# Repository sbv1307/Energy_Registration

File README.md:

# **Energy registration**
###### **Version 2.0.0**

This Arduino project will monitor the open collector output on a number of Carlo Gavazzi energy meters Type EM23 DIN and/or Type EM111.
The pulses will be counted and turned into number of kilo watt hours (kWh).

Upon request, the pulses counted (presented in kWh) will be pushed to a Google Sheet through a local webhook (A web site which basically "translate" HPPT to HTTPS).

Each meter monitored, will be connected to a digital imput, as well as the interrupt pin (See Emergy Registration Schematics.pdf for details).

Upon a HTTP GET pushToGoogle request (http://<Arduino IP address>/pushToGoogle), the sketch will return a HTML webpage, showing the current meter valeus, 
and initiate a HTTP GET request towards a local webHook, with the meter values, as the GET query values.

A HTTP GET meterValue request (http://<Arduino IP address>/meterValue) will return a webpage showing the current meter valeus.
 
A HTTP GET meterValue?meter<n>=<nn>, will set the counter to the provided value for the specified energy meter.
The value <n> represent the energy meter 1-7 and nn the actual energy meter value as readden on the meter, with two dicmals but entered without the decimal seperator!
(http://<Arduino IP address>/meterValue?meter1=1234567 will set the value for energy meter number one to 12345.67)

Notes:
The sketch monitors interrupt pin 2 for a FALLING puls and then reads the defined channelPins and register pulses for each pin.
The interruptfunction has a catch: It enters a "while pin 2 is low" loop, and stays there, until the interrupt is released.
This is against all recomendations, saying Interruptfunctions should be very short. 

However, in order to handle the problem with overlapping pulses from more meters, the interruptfunction will read the channels over and over,
without re-reading channels that allready has been read active (low). This way all pulses on all channels will be read.

Example: Tree meters generate tree pulses as shown below:
```bash
          _______        _______
Meter #1:        |______|
             _______        _______
Meter #2:           |______|
                _______        _______
Meter #3:              |______|

```
A pulse from meter #1 will activate the Interrupt Service Rutine (ISR), which startes the "while pin 2 is low" loop. When the pulse on meter #2 appears, while the pulse on meter #1 is still active, the ISR will stay active, when the puls on meter #1 dissapears. Then same happens when the pulse from meter #3 appears.
The "while pin 2 is low" loop read all non-read input pins, meaning: when a pin has been read as active (LOW), then pin will be read as readden, and wil not be re-read.

When the puls (the puls in meter #3) is released, the ISR ends. Then main loop will update the counter for each readden input pin, at reset the the status for the input pin.

 Version history:
  * 2.0.0 - Arduino SW project now merged with KiCad Hardware, and this version surpports the new HW design
 *         1 - LED_BUILTIN on Pin #9 has stopped woring. Pin A3 will be used instead. LED_PIN changed to LED_PIN - 
 *             HOWEVER!!! It has turned out, that it was set incrrrectly by the entrepreter. Hovering over the LED_BULTIN variable indicate it expands to 13 and not 9.
 *             Setting LED_PIN to 9, makes the LED light.
 *             Since the Hardware prototype, was made to use PIN 17, Pin 17 will be used for LED_PIN in this version.
 *         2 - Channels extenced to 8 instead of 7. Noe includeing Pin A2 
 * 0.2.3 - BUILTIN_LED has stopped working - NEED INVESTIGATION AND CODE IMPLEMTATION
 * 0.2.2 - Post powerup data to google sheets (data, and the comment (Power Up))
 * 0.2.1 - Cleaning up entries used for verifying pulscounts - No functional changes.
 * 0.2.0 - Meters, which only gives 100 pulses pr. kWh, were registered as if they gave a thousenth. Might be an issue by adding "1.000 / (double)PPKW[ii]" (0.01) to the previous counts.
 *         Since 1.000 / "(double)PPKW[ii]" might now be exactly 0.01 but maybe 0.009nnnnnnnnn, which could sum up the deffrence.
 *         SO - This version 0.2.0 will count pulses (integers). 
 *         Notes to be taken here - Mixing the types long and int, can give strange results (sometimes).
 *          - Implement: Remove SD update after each pulsecount, marked: "// V0.1.4_change (1)" in ver. 0.1.4
 *          - Implement: Flashing LED_BUILTI handled by calls to millis(), marked : "// V0.1.4_change (3)" in ver. 0.1.4.
 *          - SD Updates are done for every 10 pulses or every 30 minutes (only if pulses have been registred).
 * 0.1.4 - In an attempt to investigate lost registrations, writing every update to SD will be changed (changes marked // V0.1.4_change):
 *         1 - Remove SD update after each pulsecount marked: // V0.1.4_change (1)
 *         2 - SD is updated after each call to HTTP GET meterValue request (http://<Arduino IP address>/meterValue) marked: // V0.1.4_change (2)
 *         3 - Flashing the LED_BUILTI has handeled by the time it took to write to SD. Flashing LED_BUILTI will be handled by calls to millis() marked : // V0.1.4_change (3)
 * 
 * 0.1.3 - Due to capacity limitations in version 0.1.2, this version build upon version 0.1.1
 *       - This version is to trace why pulse registrations are lost.
 *       - Screesed in the HTML <form> element form Version 0.2.1 - Makes energymeter settings much easier
 *       - Dividing entered metervalues by 100, to avodi having to enter dicimal point (a dot) when enter metervalues
 *       - Corrected BUGs in getQuery(EthernetClient localWebClient)
 *       - Error dinvestigations marked: TO_BE_REMOVED
 *       - Added further #ifdef sections.
 *       - Inserted a function call to setMeterDataDefaults in function getQuery. If Metervalue for Meter 1 is nigative, metervalues are reset
 * 0.1.2 - N O T E !!!! - Changes exceeded limit for: Low memory available, stability problems may occur.
 *         Change in HTML presentation of energy meter values. Describing text. e.g. "Værksted" added to the informaiotn: "Meter <n>".
 *       - Introduces IP configuration for Arduino Ethernet shield attached to Arduino UNO. Define ARDUINO_UNO_DEBUG
 * 0.1.1 - Web server and web client funktionality added.
 * 0.1.0 - Initial commit - This versino is a merger of two lab tests: "EnergyRegistration" and "LocalWebHook-with-server-for-Arduino".

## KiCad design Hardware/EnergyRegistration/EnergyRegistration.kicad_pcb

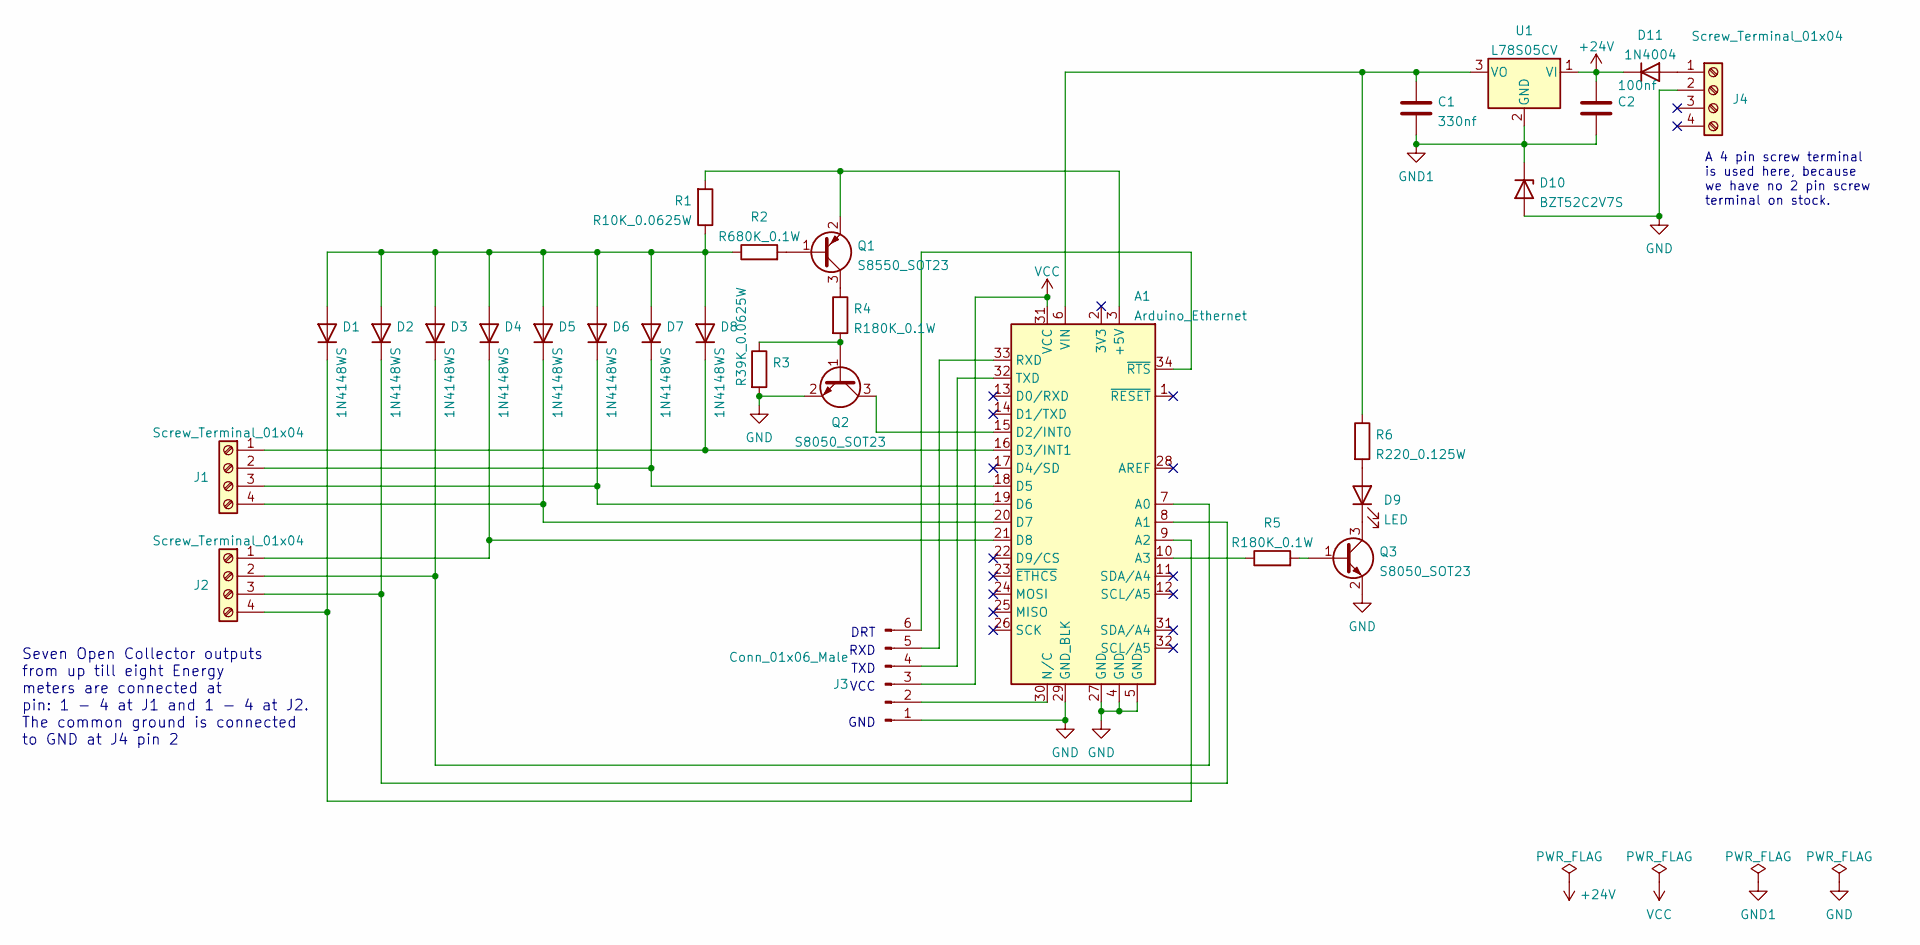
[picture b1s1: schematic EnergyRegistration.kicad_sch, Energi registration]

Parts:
A1: Arduino_Ethernet; Arduino_Ethernet_WithMountingHoles
C1: 330nf; C_0805_2012Metric; Manufacturer PN 0805B334K500NT; JLCPCB Part # C1740
C2: 100nf; C_0805_2012Metric; Manufacturer PN CC0805KRX7R9BB104; JLCPCB Part # C49678
D1, D2, D3, D4, D5, D6, D7, D8: 1N4148WS; D_SOD-323F; Manufacturer PN 1N4148WS; Digi-Key 1N4148WS-FDICT-ND
D9: LED; LED_D3.0mm; Manufacturer PN TJ-L3FYTGCGMCGLFLC2G-A5; JLCPCB Part # C331056
D10: BZT52C2V7S; D_SOD-123; Manufacturer PN BZT52C2V7S; JLCPCB Part # C353539
D11: 1N4004; D_DO-41_SOD81_P12.70mm_Horizontal; Manufacturer PN 1N4004B-G; Digi-Key Order no.: 641-1999-ND
J1, J2, J4: Screw_Terminal_01x04; TerminalBlock_PT-1,5-4-5.0-H_1x04_P5.00mm_Horizontal-(Front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
J3: Conn_01x06_Male; PinHeader_1x06_P_0,1in_Vertical
Q1: S8550_SOT23; SOT-23; Manufacturer PN S8550; JLCPCB Part # C105432
Q2, Q3: S8050_SOT23; SOT-23; Manufacturer PN SS8050; JLCPCB Part # C2150
R1: R10K_0.0625W; R_0603_1608Metric; Manufacturer PN 0402WGF1002TCE; JLCPCB Part # C25744
R2: R680K_0.1W; R_0603_1608Metric; Manufacturer PN 0603WAF6803T5E; JLCPCB Part # C25822
R3: R39K_0.0625W; R_0402_1005Metric; Manufacturer PN 0402WGF3902TCE; JLCPCB Part # C25783
R4, R5: R180K_0.1W; R_0603_1608Metric; Manufacturer PN 0603WAF1803T5E; JLCPCB Part # C22827
R6: R220_0.125W; R_0805_2012Metric; Manufacturer PN 0805W8F2200T5E; JLCPCB Part # C17557
U1: L78S05CV; TO-220-3_Vertical; Digi-Key Order no.: 497-14164-ND

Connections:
+24V: C2.1, D11.1 (K), U1.1 (VI)
GND: A1.4 (GND), A1.5 (GND), A1.27 (GND), A1.29 (GND_BLK), D10.2 (A), J3.1, J4.2, Q2.2 (E), Q3.2 (E), R3.2
GND1: C1.2, C2.2, D10.1 (K), U1.2 (GND)
unnamed: A1.3 (+5V), Q1.2 (E), R1.2
unnamed: A1.6 (VIN), C1.1, R6.1, U1.3 (VO)
unnamed: A1.7 (A0), D3.1 (K), J2.2
unnamed: A1.8 (A1), D2.1 (K), J2.3
unnamed: A1.9 (A2), D1.1 (K), J2.4
unnamed: A1.10 (A3), R5.1
unnamed: A1.15 (D2/INT0), Q2.3 (C)
unnamed: A1.16 (D3/INT1), D8.1 (K), J1.1
unnamed: A1.18 (D5), D7.1 (K), J1.2
unnamed: A1.19 (D6), D6.1 (K), J1.3
unnamed: A1.20 (D7), D5.1 (K), J1.4
unnamed: A1.21 (D8), D4.1 (K), J2.1
unnamed: A1.30 (N/C), J3.2
unnamed: A1.32 (TXD), J3.4
unnamed: A1.33 (RXD), J3.5
unnamed: A1.34 (~RTS), J3.6
unnamed: D1.2 (A), D2.2 (A), D3.2 (A), D4.2 (A), D5.2 (A), D6.2 (A), D7.2 (A), D8.2 (A), R1.1, R2.1
unnamed: D9.1 (K), Q3.3 (C)
unnamed: D9.2 (A), R6.2
unnamed: D11.2 (A), J4.1
unnamed: Q1.1 (B), R2.2
unnamed: Q1.3 (C), R4.1
unnamed: Q2.1 (B), R3.1, R4.2
unnamed: Q3.1 (B), R5.2
VCC: A1.31 (VCC), J3.3

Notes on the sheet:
Seven Open Collector outputs from up till eight Energy meters are connected at pin: 1 - 4 at J1 and 1 - 4 at J2. The common ground is connected to GND at J4 pin 2
A 4 pin screw terminal is used here, because we have no 2 pin screw terminal on stock.
RXD
DRT
VCC
TXD
GND

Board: 2 copper layers, 28 parts (0 on the bottom side), 27 nets, no tracks yet.

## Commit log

2020-11-20 Initial Commit Setup() and Counting module (incl. interrupt funktionality
2020-11-21 * 0.1.1 - Web server and web client funktionality added.
2020-11-22 Initial V 0.1.2 commit * 0.1.2 - Change in HTML presentation of energy meter values. Changed from: "Meter <n>" to a more describing text. e.g. "Værksted"
2020-11-22 * 0.1.2 - Change in HTML presentation of energy meter values. Describing text. e.g. "Værksted" added to the informaiotn: "Meter <n>".
2020-11-23 * 0.1.2 - N O T E !!!! - Changes exceeded limit for: Low memory available, stability problems may occur. * Change in HTML presentation of energy meter values. Describing text. e.g. "Værksted" added t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
2020-11-25 * 0.1.3 - Due to capacity limitations, this version build upon version 0.1.1 * - This version is to trace why pulse registrations are lost. * - Screesed in the HTML <form> element form Version 0.2.1 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
2020-11-26 Bug - forgot to reset pulseRegistered, which obvious causes an incorrectg count.
2022-01-25 Counts verifed
2022-01-26 Ver. 0.1.4 - removing SD updates did not solve the issue
2022-01-27 Minor documentaiton updates
2022-01-27 Version 0.2.0 commit
2022-01-31 No changes - attempt to merge
2022-01-31 remote arduino json from repo
2022-01-31 Debug entries removed
2022-01-31 remove json file form repo
2022-01-31 initial commint
2022-02-01 Post meter values to Google sheet at poser up. Cleaning up and add documentation.
2022-02-18 Files re-arranged and local repo moved
2022-02-18 Arduino and KiCad projects merged into one filestructure
2022-02-19 Vorking commit
2022-03-09 PCB Components added
2022-03-09 submudules
2022-03-09 librara update
2022-03-09 Library update
2022-03-09 fix: Change pinnumber for LED to PIN 17
2022-03-10 Components changed to SMD
